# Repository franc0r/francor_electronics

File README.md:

# francor_electronics

Electronic Components like PowerDistribution PCBs or Adapter PCBs

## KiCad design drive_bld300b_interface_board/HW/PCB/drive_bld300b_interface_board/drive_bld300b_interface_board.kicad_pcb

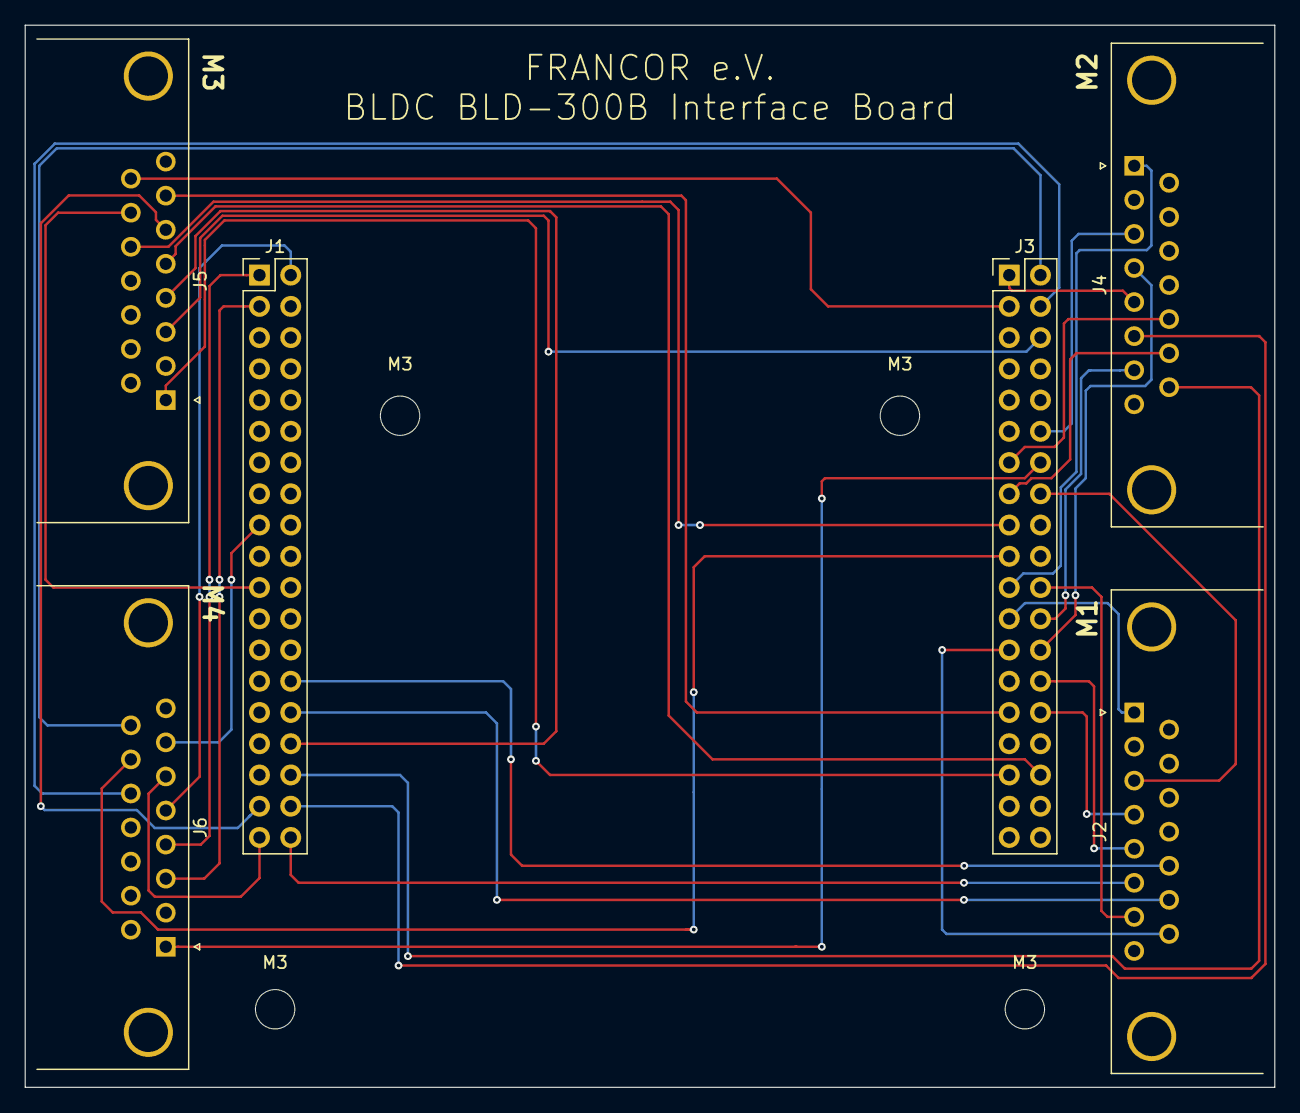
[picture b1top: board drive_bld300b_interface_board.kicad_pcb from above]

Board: 2 copper layers, 101.6 x 86.4 mm, 10 parts (0 on the bottom side), 37 nets.

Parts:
J1: N_CN7; PinHeader_2x19_P2.54mm_Vertical
J2: M1; DSUB-15_Female_Horizontal_P2.77x2.84mm_EdgePinOffset7.70mm_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
J3: N_CN10; PinHeader_2x19_P2.54mm_Vertical
J4: M2; DSUB-15_Female_Horizontal_P2.77x2.84mm_EdgePinOffset7.70mm_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
J5: M3; DSUB-15_Female_Horizontal_P2.77x2.84mm_EdgePinOffset7.70mm_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
J6: M4; DSUB-15_Female_Horizontal_P2.77x2.84mm_EdgePinOffset7.70mm_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
M3, M3#2, M3#3, M3#4: M3; MountingHole_3.2mm_M3

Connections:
/M1_ALM: J2.7, J3.22
/M1_BRK: J2.5, J3.28
/M1_DIR: J2.3, J3.16
/M1_EN: J2.4, J3.30
/M1_HA: J1.28, J2.13
/M1_HB: J1.30, J2.14
/M1_HC: J2.15, J3.25
/M1_PWM: J2.1, J3.23
/M1_SPD: J1.38, J2.6
/M2_ALM: J3.24, J4.7
/M2_BRK: J3.1, J4.5
/M2_DIR: J3.12, J4.3
/M2_EN: J3.26, J4.4
/M2_HA: J3.13, J4.13
/M2_HB: J3.15, J4.14
/M2_HC: J1.34, J4.15
/M2_PWM: J3.21, J4.1
/M2_SPD: J1.36, J4.6
/M3_ALM: J3.29, J5.7
/M3_BRK: J3.34, J5.5
/M3_DIR: J3.6, J5.3
/M3_EN: J1.32, J5.4
/M3_HA: J3.17, J5.13
/M3_HB: J1.21, J5.14
/M3_HC: J3.3, J5.15
/M3_PWM: J3.33, J5.1
/M3_SPD: J1.35, J5.6
/M4_ALM: J1.17, J6.7
/M4_BRK: J1.2, J6.5
/M4_DIR: J1.3, J6.3
/M4_EN: J1.1, J6.4
/M4_HA: J3.4, J6.13
/M4_HB: J3.19, J6.14
/M4_HC: J3.2, J6.15
/M4_PWM: J3.14, J6.1
/M4_SPD: J1.37, J6.6
GND: J1.8, J1.19, J1.20, J1.22, J2.0, J2.2, J3.9, J3.20, J3.32, J4.0, J4.2, J5.0, J5.2, J6.0, J6.2

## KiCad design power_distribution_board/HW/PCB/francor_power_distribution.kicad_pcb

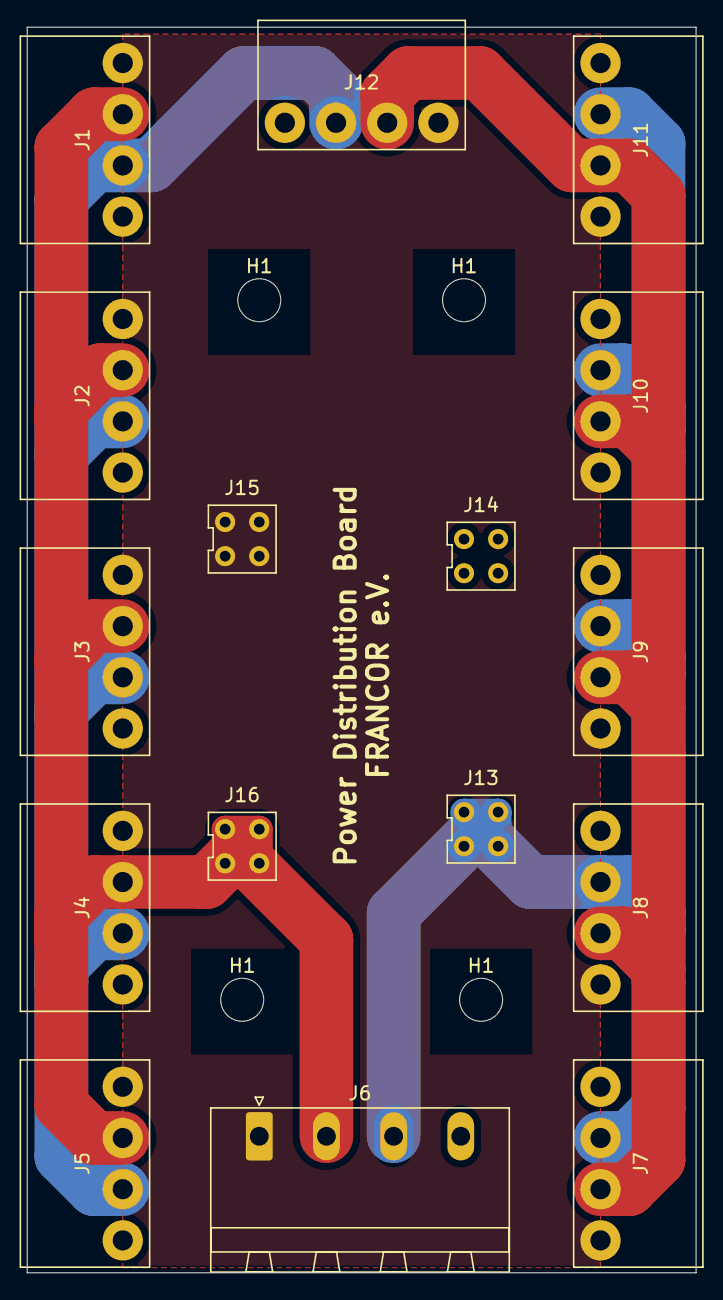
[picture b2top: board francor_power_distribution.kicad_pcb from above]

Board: 2 copper layers, 49.8 x 92.7 mm, 20 parts (0 on the bottom side), 4 nets.

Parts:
H1, H1#2, H1#3, H1#4: M3; MountingHole_3.2mm_M3
J1, J2, J3, J4, J5, J7, J8, J9, J10, J11, J12: Conn_01x04_3.81; Conn_01x04_4mm
J6: Screw_Terminal_01x04; PhoenixContact_MSTBA_2,5_4-G_1x04_P5.00mm_Horizontal
J13, J14, J15, J16: ESQ-102-24-T-D

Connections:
/GND: J1.4, J2.4, J3.4, J4.4, J5.4, J6.4, J7.4, J8.4, J9.4, J10.4, J11.4, J12.4, J14.1, J14.2, J14.3, J14.4
/HPWR: J1.1, J2.1, J3.1, J4.1, J5.1, J6.1, J7.1, J8.1, J9.1, J10.1, J11.1, J12.1, J15.1, J15.2, J15.3, J15.4
/MPWR1: J1.2, J2.2, J3.2, J4.2, J5.2, J6.2, J7.2, J8.2, J9.2, J10.2, J11.2, J12.2, J16.1, J16.2, J16.3, J16.4
/MPWR2: J1.3, J2.3, J3.3, J4.3, J5.3, J6.3, J7.3, J8.3, J9.3, J10.3, J11.3, J12.3, J13.1, J13.2, J13.3, J13.4

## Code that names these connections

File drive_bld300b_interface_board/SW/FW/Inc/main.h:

/* USER CODE BEGIN Header */
/**
  ******************************************************************************
  * @file           : main.h
  * @brief          : Header for main.c file.
  *                   This file contains the common defines of the application.
  ******************************************************************************
  * @attention
  *
  * <h2><center>&copy; Copyright (c) 2019 STMicroelectronics.
  * All rights reserved.</center></h2>
  *
  * This software component is licensed by ST under BSD 3-Clause license,
  * the "License"; You may not use this file except in compliance with the
  * License. You may obtain a copy of the License at:
  *                        opensource.org/licenses/BSD-3-Clause
  *
  ******************************************************************************
  */
/* USER CODE END Header */

/* Define to prevent recursive inclusion -------------------------------------*/
#ifndef __MAIN_H
#define __MAIN_H

#ifdef __cplusplus
extern "C" {
#endif

/* Includes ------------------------------------------------------------------*/
#include "stm32f4xx_hal.h"

/* Private includes ----------------------------------------------------------*/
/* USER CODE BEGIN Includes */

/* USER CODE END Includes */

/* Exported types ------------------------------------------------------------*/
/* USER CODE BEGIN ET */

/* USER CODE END ET */

/* Exported constants --------------------------------------------------------*/
/* USER CODE BEGIN EC */

/* USER CODE END EC */

/* Exported macro ------------------------------------------------------------*/
/* USER CODE BEGIN EM */

/* USER CODE END EM */

void HAL_TIM_MspPostInit(TIM_HandleTypeDef *htim);

/* Exported functions prototypes ---------------------------------------------*/
void Error_Handler(void);

/* USER CODE BEGIN EFP */

/* USER CODE END EFP */

/* Private defines -----------------------------------------------------------*/
#define B1_Pin GPIO_PIN_13
#define B1_GPIO_Port GPIOC
#define M1_SPD_Pin GPIO_PIN_0
#define M1_SPD_GPIO_Port GPIOC
#define M1_SPD_EXTI_IRQn EXTI0_IRQn
#define M2_SPD_Pin GPIO_PIN_1
#define M2_SPD_GPIO_Port GPIOC
#define M2_SPD_EXTI_IRQn EXTI1_IRQn
#define M3_SPD_Pin GPIO_PIN_2
#define M3_SPD_GPIO_Port GPIOC
#define M3_SPD_EXTI_IRQn EXTI2_IRQn
#define M4_SPD_Pin GPIO_PIN_3
#define M4_SPD_GPIO_Port GPIOC
#define M4_SPD_EXTI_IRQn EXTI3_IRQn
#define M1_HA_Pin GPIO_PIN_0
#define M1_HA_GPIO_Port GPIOA
#define M1_HB_Pin GPIO_PIN_1
#define M1_HB_GPIO_Port GPIOA
#define USART_TX_Pin GPIO_PIN_2
#define USART_TX_GPIO_Port GPIOA
#define USART_RX_Pin GPIO_PIN_3
#define USART_RX_GPIO_Port GPIOA
#define M3_EN_Pin GPIO_PIN_4
#define M3_EN_GPIO_Port GPIOA
#define LD2_Pin GPIO_PIN_5
#define LD2_GPIO_Port GPIOA
#define M2_HA_Pin GPIO_PIN_6
#define M2_HA_GPIO_Port GPIOA
#define M2_HB_Pin GPIO_PIN_7
#define M2_HB_GPIO_Port GPIOA
#define M3_BRK_Pin GPIO_PIN_4
#define M3_BRK_GPIO_Port GPIOC
#define M3_DIR_Pin GPIO_PIN_5
#define M3_DIR_GPIO_Port GPIOC
#define M2_HC_Pin GPIO_PIN_0
#define M2_HC_GPIO_Port GPIOB
#define M2_ALM_Pin GPIO_PIN_1
#define M2_ALM_GPIO_Port GPIOB
#define M1_ALM_Pin GPIO_PIN_2
#define M1_ALM_GPIO_Port GPIOB
#define M1_HC_Pin GPIO_PIN_10
#define M1_HC_GPIO_Port GPIOB
#define M1_DIR_Pin GPIO_PIN_12
#define M1_DIR_GPIO_Port GPIOB
#define M1_EN_Pin GPIO_PIN_13
#define M1_EN_GPIO_Port GPIOB
#define M1_BRK_Pin GPIO_PIN_14
#define M1_BRK_GPIO_Port GPIOB
#define M2_EN_Pin GPIO_PIN_15
#define M2_EN_GPIO_Port GPIOB
#define M4_HA_Pin GPIO_PIN_6
#define M4_HA_GPIO_Port GPIOC
#define M4_HB_Pin GPIO_PIN_7
#define M4_HB_GPIO_Port GPIOC
#define M4_HC_Pin GPIO_PIN_8
#define M4_HC_GPIO_Port GPIOC
#define M2_BRK_Pin GPIO_PIN_9
#define M2_BRK_GPIO_Port GPIOC
#define M1_PWM_Pin GPIO_PIN_8
#define M1_PWM_GPIO_Port GPIOA
#define M2_PWM_Pin GPIO_PIN_9
#define M2_PWM_GPIO_Port GPIOA
#define M3_PWM_Pin GPIO_PIN_10
#define M3_PWM_GPIO_Port GPIOA
#define M4_PWM_Pin GPIO_PIN_11
#define M4_PWM_GPIO_Port GPIOA
#define M2_DIR_Pin GPIO_PIN_12
#define M2_DIR_GPIO_Port GPIOA
#define TMS_Pin GPIO_PIN_13
#define TMS_GPIO_Port GPIOA
#define TCK_Pin GPIO_PIN_14
#define TCK_GPIO_Port GPIOA
#define M4_ALM_Pin GPIO_PIN_15
#define M4_ALM_GPIO_Port GPIOA
#define M4_EN_Pin GPIO_PIN_10
#define M4_EN_GPIO_Port GPIOC
#define M4_BRK_Pin GPIO_PIN_11
#define M4_BRK_GPIO_Port GPIOC
#define M4_DIR_Pin GPIO_PIN_12
#define M4_DIR_GPIO_Port GPIOC
#define SWO_Pin GPIO_PIN_3
#define SWO_GPIO_Port GPIOB
#define M3_ALM_Pin GPIO_PIN_5
#define M3_ALM_GPIO_Port GPIOB
#define M3_HA_Pin GPIO_PIN_6
#define M3_HA_GPIO_Port GPIOB
#define M3_HB_Pin GPIO_PIN_7
#define M3_HB_GPIO_Port GPIOB
#define M3_HC_Pin GPIO_PIN_8
#define M3_HC_GPIO_Port GPIOB
/* USER CODE BEGIN Private defines */

/* USER CODE END Private defines */

#ifdef __cplusplus
}
#endif

#endif /* __MAIN_H */

/************************ (C) COPYRIGHT STMicroelectronics *****END OF FILE****/

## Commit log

2019-04-05 Added PCB of power distribution board
2019-04-05 Added BOM
2019-04-07 Added CubeMX project and pin assigment list
2019-04-07 Added pin assigment to scheme
2019-04-07 Added scheme and PCB
2019-04-07 Finished PCB
2019-04-07 Added text to PCBs
2019-04-08 Added gerber files for production
2019-04-08 JLPCB Order
2019-04-16 Started firmware development and added sources
2019-04-17 Continued development
2019-04-17 Added rpm calculation
2019-04-17 Added timer configs in CubeMX
2019-04-17 Added gitignore
2019-04-19 Changed input filters for hall encoder inputs
2019-04-19 Improved speed calculation
2019-04-19 Added controller
2019-04-19 Added support for serial interface
2019-04-19 Added timeout
2019-04-20 Added interface ROS node
2019-04-20 Moved firmware to other folder
2019-04-20 Added timeout for every drive
2019-04-20 Added launchfile and params
2019-04-20 Started developing direction determination in motorcontroller class
2019-04-20 Added high resulution timer
2019-04-20 Added UART interrupt
2019-04-21 Added support for direction calculation
2019-04-23 Small bugfix
2019-05-02 Added rosserial
2019-05-02 Changed speed input pins to pulldown
